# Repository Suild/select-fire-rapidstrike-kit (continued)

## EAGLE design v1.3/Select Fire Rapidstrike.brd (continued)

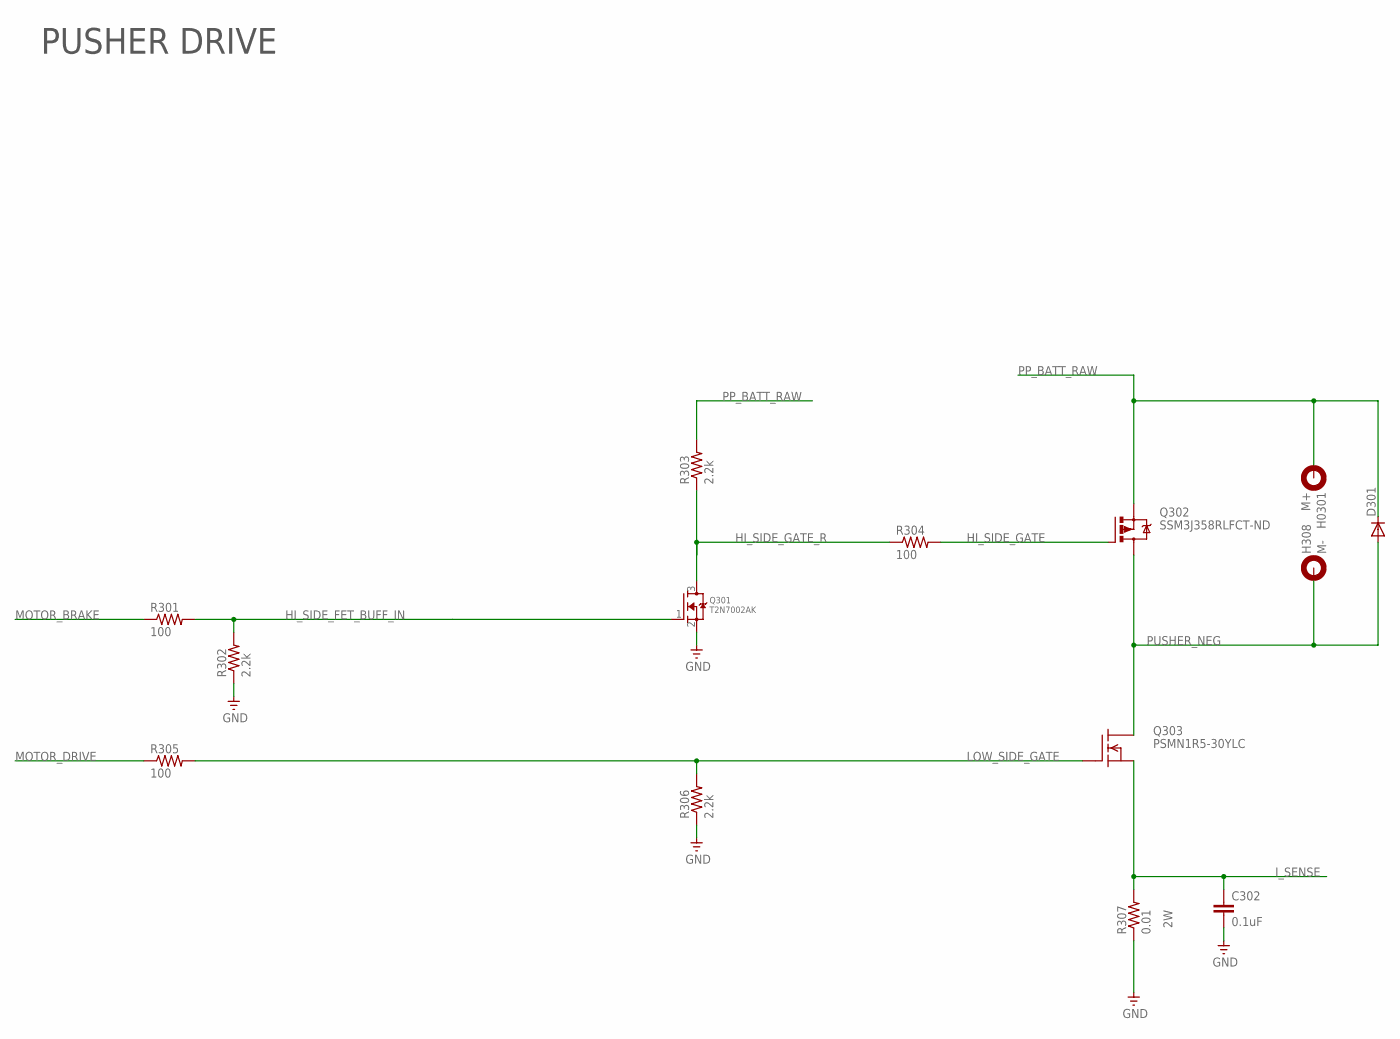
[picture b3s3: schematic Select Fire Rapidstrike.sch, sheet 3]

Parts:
C302: 0.1uF; C0805
D301: S2A; DO214AA
H0301: M+; MOUNT-HOLE-2.5MM
H308: M-; MOUNT-HOLE-2.5MM
Q301: T2N7002AK; SOT23
Q302: SSM3J358RLFCT-ND; SOT-23
Q303: PSMN1R5-30YLC; TO127P600X120-5N
R301, R304, R305: 100; M0805
R302, R303, R306: 2.2k; M0805
R307: 0.01; R2512

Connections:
GND: C302.2, Q301.2 (S), R302.1, R306.1, R307.1; also elsewhere on the board
HI_SIDE_FET_BUFF_IN: Q301.1 (G), R301.2, R302.2
HI_SIDE_GATE: Q302.1 (G), R304.2
HI_SIDE_GATE_R: Q301.3 (D), R303.1, R304.1
I_SENSE: C302.1, Q303.1 (S), Q303.2 (S), Q303.3 (S), R307.2; also elsewhere on the board
LOW_SIDE_GATE: Q303.4 (G), R305.2, R306.2
MOTOR_BRAKE: R301.1; also elsewhere on the board
MOTOR_DRIVE: R305.1; also elsewhere on the board
PP_BATT_RAW: D301.C, H0301.P$1, Q302.2 (S), R303.2; also elsewhere on the board
PUSHER_NEG: D301.A, H308.P$1, Q302.3 (D), Q303.5 (D)

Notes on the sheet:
PUSHER DRIVE

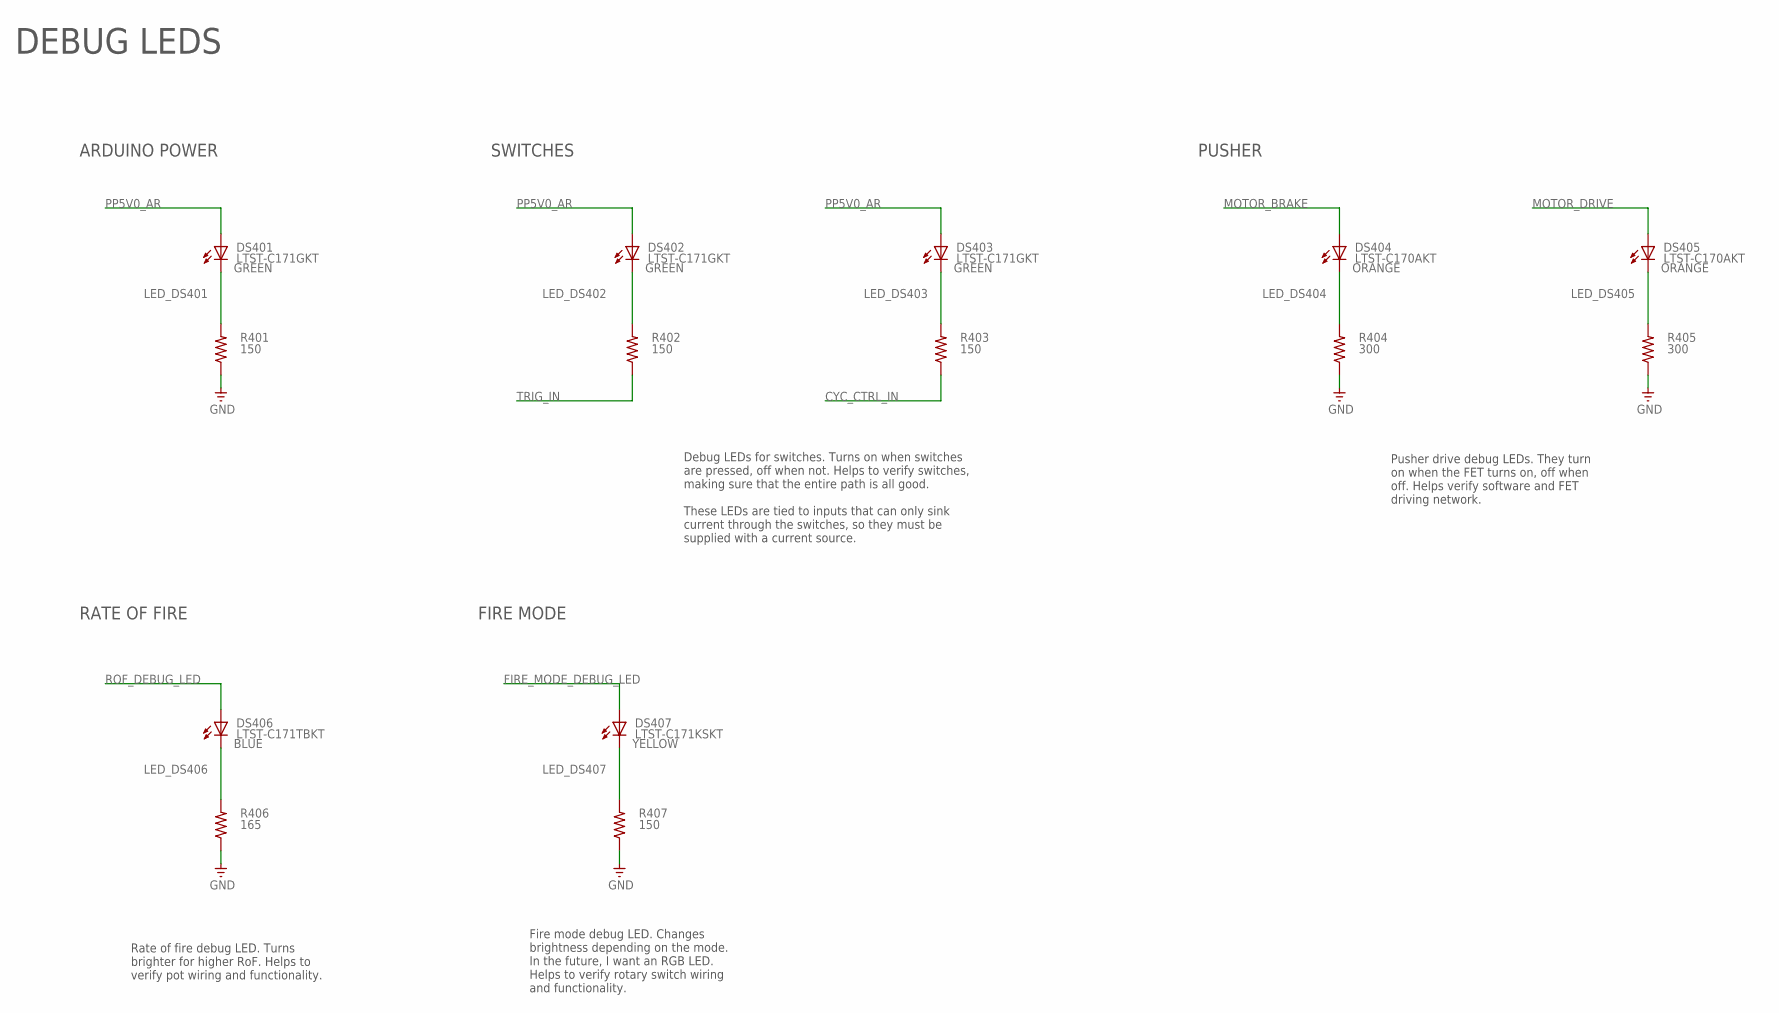
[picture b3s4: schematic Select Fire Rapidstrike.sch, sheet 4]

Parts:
DS401, DS402, DS403: LTST-C171GKT; CHIPLED_0805
DS404, DS405: LTST-C170AKT; CHIPLED_0805
DS406: LTST-C171TBKT; CHIPLED_0805
DS407: LTST-C171KSKT; CHIPLED_0805
R401, R402, R403, R407: 150; M0805
R404, R405: 300; M0805
R406: 165; M0805

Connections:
CYC_CTRL_IN: R403.1; also elsewhere on the board
FIRE_MODE_DEBUG_LED: DS407.A; also elsewhere on the board
GND: R401.1, R404.1, R405.1, R406.1, R407.1; also elsewhere on the board
LED_DS401: DS401.C, R401.2
LED_DS402: DS402.C, R402.2
LED_DS403: DS403.C, R403.2
LED_DS404: DS404.C, R404.2
LED_DS405: DS405.C, R405.2
LED_DS406: DS406.C, R406.2
LED_DS407: DS407.C, R407.2
MOTOR_BRAKE: DS404.A; also elsewhere on the board
MOTOR_DRIVE: DS405.A; also elsewhere on the board
PP5V0_AR: DS401.A, DS402.A, DS403.A; also elsewhere on the board
ROF_DEBUG_LED: DS406.A; also elsewhere on the board
TRIG_IN: R402.1; also elsewhere on the board

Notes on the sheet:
DEBUG LEDS
Fire mode debug LED. Changes brightness depending on the mode. In the future, I want an RGB LED. Helps to verify rotary switch wiring and functionality.
Debug LEDs for switches. Turns on when switches are pressed, off when not. Helps to verify switches, making sure that the entire path is all good. These LEDs are tied to inputs that can only sink current through the switches, so they must be supplied with a current source.
Rate of fire debug LED. Turns brighter for higher RoF. Helps to verify pot wiring and functionality.
Pusher drive debug LEDs. They turn on when the FET turns on, off when off. Helps verify software and FET driving network.
SWITCHES
ARDUINO POWER
PUSHER
RATE OF FIRE
FIRE MODE

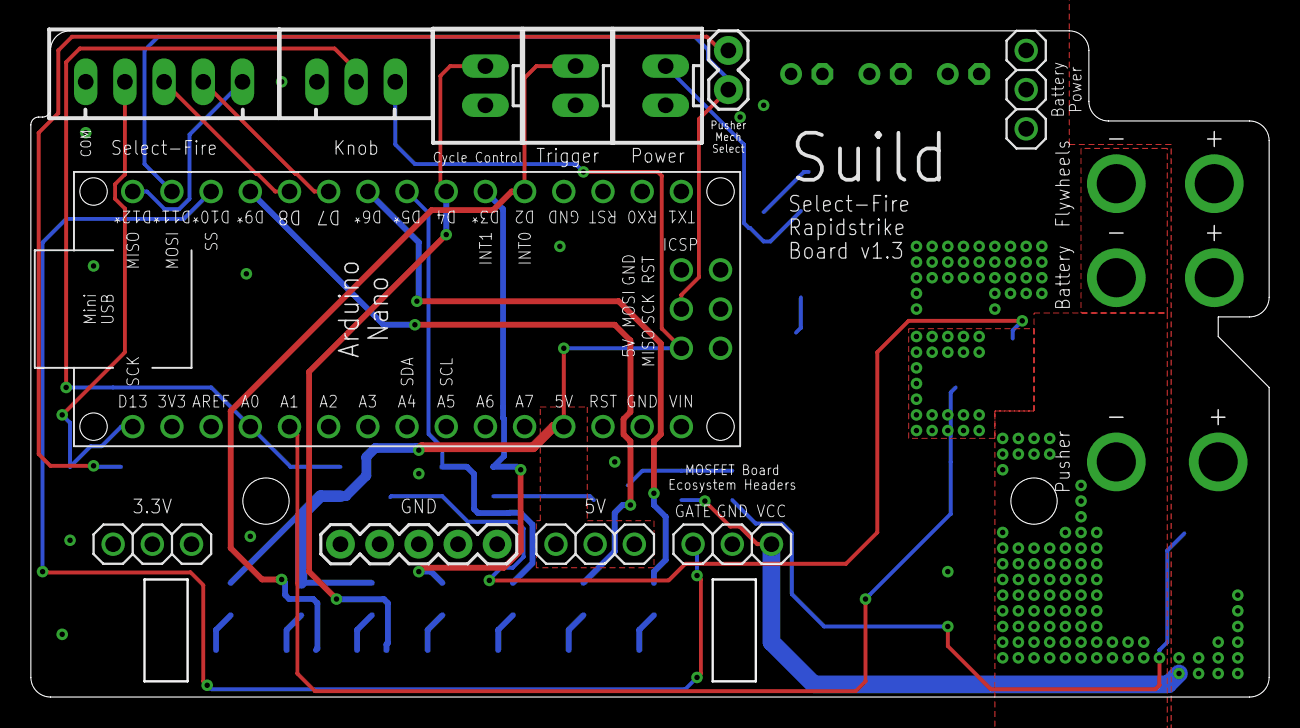
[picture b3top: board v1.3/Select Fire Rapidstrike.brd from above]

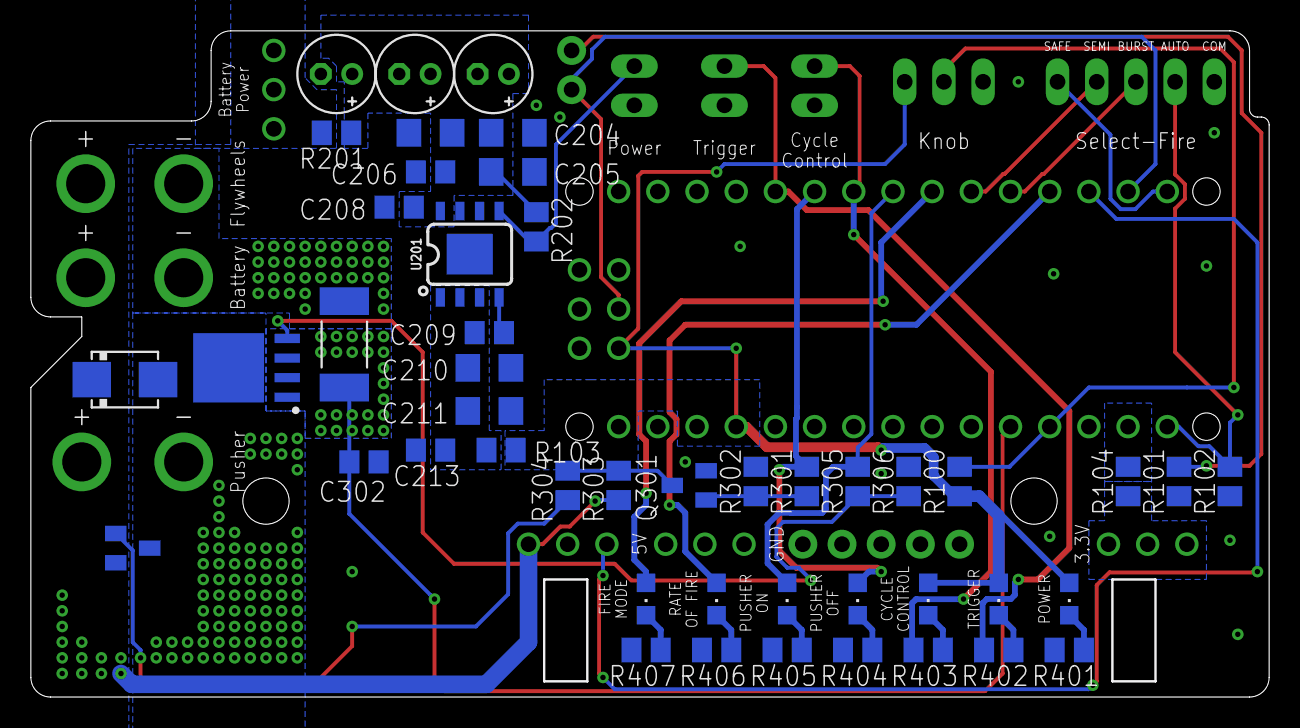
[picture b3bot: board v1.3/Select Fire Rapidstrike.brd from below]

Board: 2 copper layers, 80.3 x 43.2 mm, 66 parts (47 on the bottom side), 36 nets.

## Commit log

2019-06-29 add hardware files for v0.1
2019-06-29 move select-fire RS v0.1 sch and brd files to their respective folders
2019-06-29 Update README.md
    Add buy link, initial image, and product description.
2019-07-20 add v0.1 firmware and tests
2019-09-08 add firmware for select-fire rapidstrike kit v1.0
2019-09-08 add select-fire rapidstrike v0.2 board and schematics eagle files
2019-09-08 move select-fire RS v1.0 firmware to software folder
2019-09-08 add board files, images, and schematics for Select-Fire RS v1.0
2019-10-24 add hardware files for v1.1 variant
2020-04-07 Add wiring diagram for flywheel motors with microswitch
2020-04-18 add hardware files for v1.2
2020-04-18 add hardware files for v1.3
2020-04-18 refactor and rename a few files
2020-07-11 Add wiring diagram for a voltmeter with kill switch
